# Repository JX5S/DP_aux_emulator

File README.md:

# DP-aux emulator

Hardware design files for a DP-aux emulation board, designed to allow connection of PSVR2 headsets to PC.

# Why

Prior to a March 2024 update of the PSVR2's firmware, the headset reported incorrect information via DP-aux, among others the EDID and DSC capability. A custom EDID can be set without additional hardware, however DSC options cannot be - so the emulator board was born.

# Status as of June 2024

Since this board was built, Sony released firmware update(s) to the PSVR2, which corrected the lies and allow connection to GPUs directly. While this emulator is still useful for enabling "cinema" mode and for future experiments, such as possibly enabling HDR support, most users won't need it.

This board is only for modifying traffic on DP-aux, it doesn't help if your GPU doesn't have a USB-C port. Sony is releasing an adapter for that soon, I have no reason to believe it wouldn't work with 3rd party drivers.

This is a third revision of the PCB, it has been verified to work as designed.

# Everything you need to build some

## PCBs

The board was designed for JLCPCB's assembly. The necessary files are in the ['Manufacturing data'](https://github.com/JX5S/DP_aux_emulator/tree/main/Manufacturing%20data) folder. The zip file is there for a quick download of just those 3 files. The files are:

- ...-Gerbers.zip = Manufacturing data for the circuit board
- ...-BOM.csv = a list of components that need mounting
- ...-top-pos.csv = a list of positions of each component

The only settings that need changing from defaults during ordering at JLCPCB are PCB thickness (0.8mm) and impedance control (Yes; JLC06081H-2116). Detailed screenshots of all settings including defaults are in the ['JLCPCB settings'](https://github.com/JX5S/DP_aux_emulator/tree/main/JLCPCB%20settings) folder.

The 4th image shows edge-rail cut-outs which need to be added to allow surface mounting of these specific USB-C connectors. These can be added by JLC (you do need to explicitly request them), or you can add them yourself in KiCad, or you can have the edge-rails removed and the USB-C connectors added afterwards (JLC will build a mounting adapter for the board at additional cost).

## Firmware

Firmware was written by the autor of the [iVRy SteamVR driver](https://store.steampowered.com/app/992490). A passthrough-only version of the firmware is provided in this repository for testing, a PSVR2-specific firmware is distributed along with the [iVRy PSVR2 driver](https://store.steampowered.com/app/2772740).

## 3D-Printed case

A case has been designed for the DP-AUX emulator by "Hackinside". They have kindly [made the files available](https://www.pcbway.com/project/shareproject/iVRy_PSVR2_DP_AUX_Emulator_Enclosure_case_ef058b5b.html) for anyone that wants to print their own case.

# How it works

On the PCB is an RP2040 microcontroller, which decides which DP-aux requests to modify and which to pass through unchanged. To interface with DP-aux, a pair of SN65MLVD200A differential transceivers are used. The LVDS part of the circuit is based on Bitec's DisplayPort Daughter Card.

Apart from the core DP-aux emulation circuitry, there is a programming micro-USB connector (I would have used a USB-C, but this way it cannot be confused with the PSVR2 port), orientation detection using USB-C CC pins, and a power section, allowing the board to be powered with either the programming USB port or using VBUS from the USB-Cs. Even though the board was made with specifically the PSVR2 in mind, I tried to make it as compliant as possible with a low part count and it should work well with the maximum voltage of USB-PD3.0, 21V.

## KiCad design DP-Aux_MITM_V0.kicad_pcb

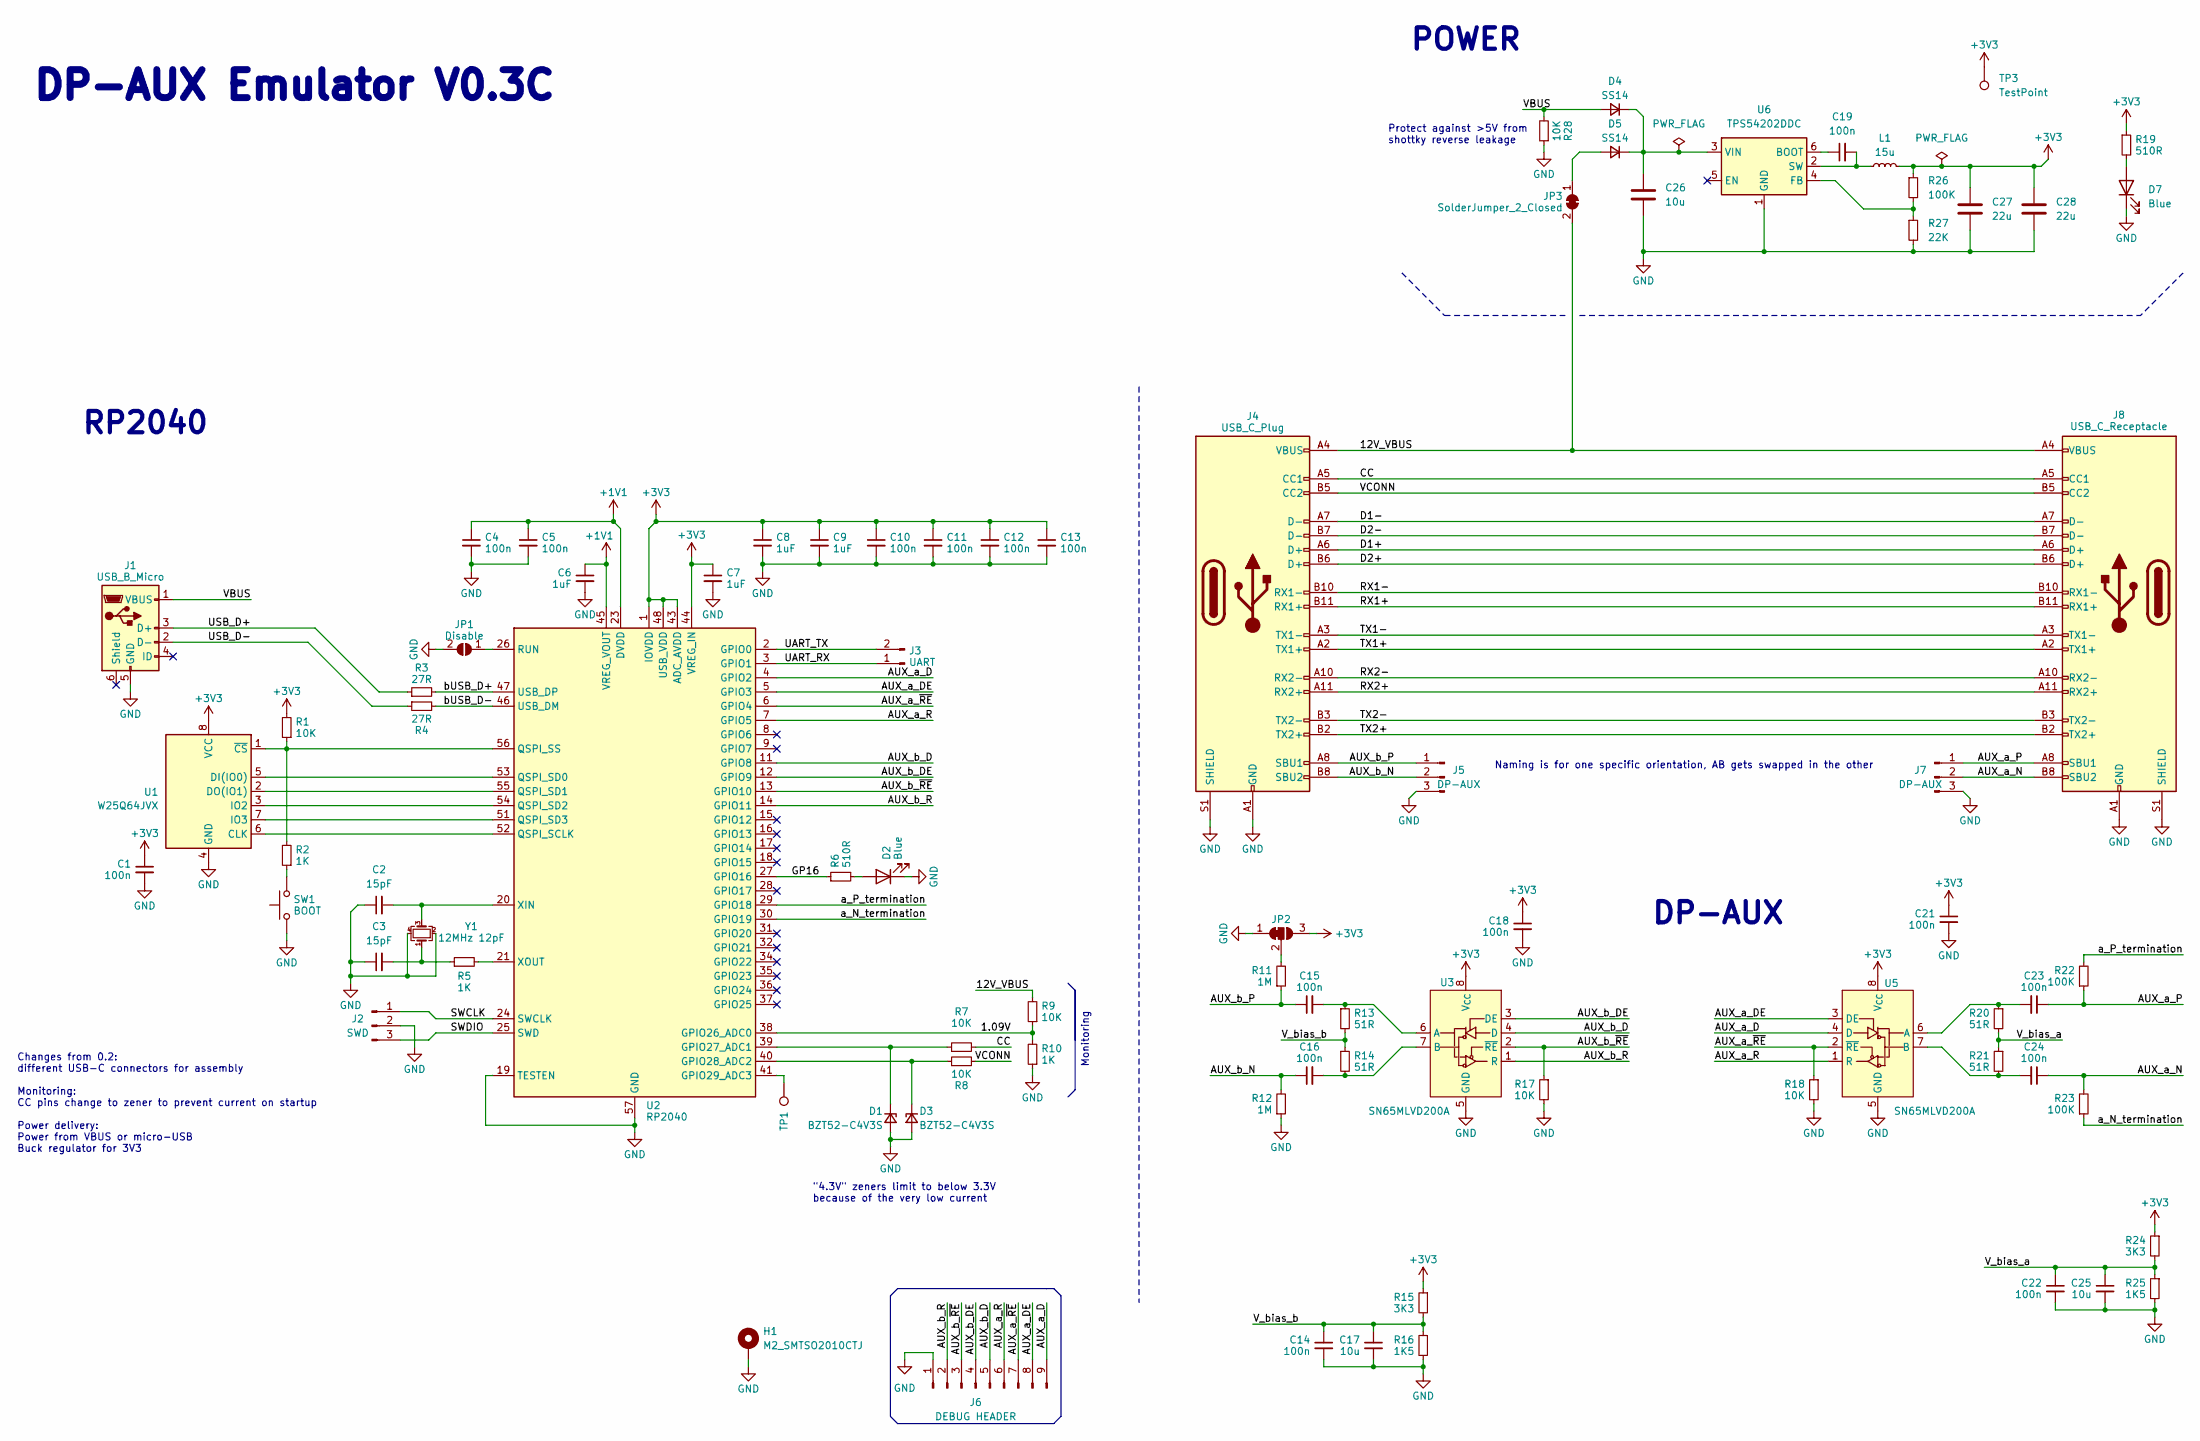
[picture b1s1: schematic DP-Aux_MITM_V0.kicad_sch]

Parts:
C1, C4, C5, C10, C11, C12, C13, C14, C15, C16, C18, C19, C21, C22, C23, C24: 100n; C_0402_1005Metric; LCSC C307331
C2, C3: 15pF; C_0402_1005Metric; LCSC C1548
C6, C7, C8, C9: 1uF; C_0402_1005Metric; LCSC C52923
C17, C25: 10u; C_0603_1608Metric; LCSC C19702
C26: 10u; C_0805_2012Metric; LCSC C15850
C27, C28: 22u; C_0805_2012Metric; LCSC C45783
D1, D3: BZT52-C4V3S; D_SOD-323 Panjit; LCSC C398771
D2, D7: Blue; LED_0603_1608Metric; LCSC C72041
D4, D5: SS14; D_SOD-123FL; LCSC C2909920
H1: M2_SMTSO2010CTJ; M2 solder nut; LCSC C2916319
J1: USB_B_Micro; USB_Micro-B_Molex-105017-0001; LCSC C132563
J2: SWD; PinHeader_1x03_P2.54mm_Vertical; LCSC DNP
J3: UART; PinHeader_1x02_P2.54mm_Vertical; LCSC DNP
J4: USB_C_Plug; USB_C_VirtualLink_Plug; LCSC C319150
J5, J7: DP-AUX; PinHeader_1x03_P2.54mm_Vertical; LCSC DNP
J6: DEBUG HEADER; PinHeader_1x09_P2.54mm_Vertical; LCSC DNP
J8: USB_C_Receptacle; USB_C_Straddle_Socket; LCSC C309352
JP1: Disable; SolderJumper-2_P1.3mm_Open_RoundedPad1.0x1.5mm; LCSC DNP
JP2: SolderJumper_3_Bridged12; SolderJumper-3_P1.3mm_Bridged2Bar12_RoundedPad1.0x1.5mm; LCSC DNP
JP3: SolderJumper_2_Closed; SolderJumper-2_P1.3mm_Bridged2Bar_RoundedPad1.0x1.5mm; LCSC DNP
L1: 15u; L_Sunlord_SWPA4018S; LCSC C436651
R1, R7, R8, R9, R17, R18, R28: 10K; R_0402_1005Metric; LCSC C25744
R2, R5, R10: 1K; R_0402_1005Metric; LCSC C11702
R3, R4: 27R; R_0603_1608Metric; LCSC C25190
R6, R19: 510R; R_0402_1005Metric; LCSC C25123
R11, R12: 1M; R_0402_1005Metric; LCSC C26083
R13, R14, R20, R21: 51R; R_0402_1005Metric; LCSC C25125
R15, R24: 3K3; R_0402_1005Metric; LCSC C25890
R16, R25: 1K5; R_0402_1005Metric; LCSC C25867
R22, R23, R26: 100K; R_0402_1005Metric; LCSC C25741
R27: 22K; R_0402_1005Metric; LCSC C25768
SW1: BOOT; C&K KMR223GLFG; LCSC C221678
TP1: TestPoint; TestPoint_Pad_D2.0mm; LCSC DNP
TP3: TestPoint; TestPoint_Loop_D1.80mm_Drill1.0mm_Beaded; LCSC C238122
U1: W25Q64JVX; WSON-8-1EP_4x4mm_P0.8mm_EP2.6x3mm; LCSC C2940195
U2: RP2040; QFN-56-1EP_7x7mm_P0.4mm_EP3.2x3.2mm; LCSC C2040
U3, U5: SN65MLVD200A; SOIC-8_3.9x4.9mm_P1.27mm; LCSC SN65MLVD200A
U6: TPS54202DDC; SOT-23-6; LCSC C191884
Y1: 12MHz 12pF; Crystal_SMD_2520-4Pin_2.5x2.0mm; LCSC C479184

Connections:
+1V1: C4.1, C5.1, C6.1, U2.23 (DVDD), U2.45 (VREG_VOUT), U2.50 (DVDD)
+3V3: C1.1, C7.1, C8.1, C9.1, C10.1, C11.1, C12.1, C13.1, C18.1, C21.1, C27.1, C28.1, JP2.3 (B), L1.2, R1.2, R15.1, R19.1, R24.1, R26.1, TP3.1, U1.8 (VCC), U2.1 (IOVDD), U2.10 (IOVDD), U2.22 (IOVDD), U2.33 (IOVDD), U2.42 (IOVDD), U2.43 (ADC_AVDD), U2.44 (VREG_IN), U2.48 (USB_VDD), U2.49 (IOVDD), U3.8 (V_{CC}), U5.8 (V_{CC})
/1.09V: R9.1, R10.2, U2.38 (GPIO26_ADC0)
/12V_VBUS: J4.A4 (VBUS), J4.A9 (VBUS), J4.B4 (VBUS), J4.B9 (VBUS), J8.A4 (VBUS), J8.A9 (VBUS), J8.B4 (VBUS), J8.B9 (VBUS), JP3.2 (B), R9.2
/AUX_a_D: J6.9, U2.4 (GPIO2), U5.4 (D)
/AUX_a_DE: J6.8, U2.5 (GPIO3), U5.3 (DE)
/AUX_a_N: C24.1, J7.2, J8.B8 (SBU2), R23.2
/AUX_a_P: C23.1, J7.1, J8.A8 (SBU1), R22.1
/AUX_a_R: J6.6, U2.7 (GPIO5), U5.1 (R)
/AUX_a_~RE: J6.7, R18.1, U2.6 (GPIO4), U5.2 (~RE)
/AUX_b_D: J6.5, U2.11 (GPIO8), U3.4 (D)
/AUX_b_DE: J6.4, U2.12 (GPIO9), U3.3 (DE)
/AUX_b_N: C16.1, J4.B8 (SBU2), J5.2, R12.2
/AUX_b_P: C15.1, J4.A8 (SBU1), J5.1, R11.1
/AUX_b_R: J6.2, U2.14 (GPIO11), U3.1 (R)
/AUX_b_~RE: J6.3, R17.1, U2.13 (GPIO10), U3.2 (~RE)
/CC: J4.A5 (CC1), J8.A5 (CC1), R7.2
/D1+: J4.A6 (D+), J8.A6 (D+)
/D1-: J4.A7 (D-), J8.A7 (D-)
/D2+: J4.B6 (D+), J8.B6 (D+)
/D2-: J4.B7 (D-), J8.B7 (D-)
/GP16: R6.1, U2.27 (GPIO16)
/RX1+: J4.B11 (RX1+), J8.B11 (RX1+)
/RX1-: J4.B10 (RX1-), J8.B10 (RX1-)
/RX2+: J4.A11 (RX2+), J8.A11 (RX2+)
/RX2-: J4.A10 (RX2-), J8.A10 (RX2-)
/SWCLK: J2.1, U2.24 (SWCLK)
/SWDIO: J2.3, U2.25 (SWD)
/TX1+: J4.A2 (TX1+), J8.A2 (TX1+)
/TX1-: J4.A3 (TX1-), J8.A3 (TX1-)
/TX2+: J4.B2 (TX2+), J8.B2 (TX2+)
/TX2-: J4.B3 (TX2-), J8.B3 (TX2-)
/UART_RX: J3.1, U2.3 (GPIO1)
/UART_TX: J3.2, U2.2 (GPIO0)
/USB_D+: J1.3 (D+), R3.1
/USB_D-: J1.2 (D-), R4.1
/VBUS: D4.2 (A), J1.1 (VBUS), R28.2
/VCONN: J4.B5 (CC2), J8.B5 (CC2), R8.2
/V_bias_a: C22.1, C25.1, R20.2, R21.1, R24.2, R25.1
/V_bias_b: C14.1, C17.1, R13.2, R14.1, R15.2, R16.1
/a_N_termination: R23.1, U2.30 (GPIO19)
/a_P_termination: R22.2, U2.29 (GPIO18)
/bUSB_D+: R3.2, U2.47 (USB_DP)
/bUSB_D-: R4.2, U2.46 (USB_DM)
GND: C1.2, C2.1, C3.1, C4.2, C5.2, C6.2, C7.2, C8.2, C9.2, C10.2, C11.2, C12.2, C13.2, C14.2, C17.2, C18.2, C21.2, C22.2, C25.2, C26.2, C27.2, C28.2, D1.2 (A), D2.1 (K), D3.2 (A), D7.1 (K), H1.1, J1.5 (GND), J2.2, J4.A1 (GND), J4.A12 (GND), J4.B1 (GND), J4.B12 (GND), J4.S1 (SHIELD), J5.3, J6.1, J7.3, J8.A1 (GND), J8.A12 (GND), J8.B1 (GND), J8.B12 (GND), J8.S1 (SHIELD), JP1.2 (B), JP2.1 (A), R10.1, R12.1, R16.2, R17.2, R18.2, R25.2, R27.2, R28.1, SW1.1, U1.4 (GND), U2.19 (TESTEN), U2.57 (GND), U3.5 (GND), U5.5 (GND), U6.1 (GND), Y1.2, Y1.4
unnamed: C3.2, R5.1, Y1.1
unnamed: D1.1 (K), R7.1, U2.39 (GPIO27_ADC1)
unnamed: D2.2 (A), R6.2
unnamed: D3.1 (K), R8.1, U2.40 (GPIO28_ADC2)
unnamed: C26.1, D4.1 (K), D5.1 (K), U6.3 (VIN)
unnamed: D5.2 (A), JP3.1 (A)
unnamed: D7.2 (A), R19.2
unnamed: JP1.1 (A), U2.26 (RUN)
unnamed: JP2.2 (C), R11.2
unnamed: R2.1, SW1.2
unnamed: U1.6 (CLK), U2.52 (QSPI_SCLK)
unnamed: U1.5 (DI(IO0)), U2.53 (QSPI_SD0)
unnamed: U1.2 (DO(IO1)), U2.55 (QSPI_SD1)
unnamed: U1.3 (IO2), U2.54 (QSPI_SD2)
unnamed: U1.7 (IO3), U2.51 (QSPI_SD3)
unnamed: R1.1, R2.2, U1.1 (~CS), U2.56 (QSPI_SS)
unnamed: TP1.1, U2.41 (GPIO29_ADC3)
unnamed: C2.2, U2.20 (XIN), Y1.3
unnamed: R5.2, U2.21 (XOUT)
unnamed: C15.2, R13.1, U3.6 (A)
unnamed: C16.2, R14.2, U3.7 (B)
unnamed: C23.2, R20.1, U5.6 (A)
unnamed: C24.2, R21.2, U5.7 (B)
unnamed: C19.1, U6.6 (BOOT)
unnamed: R26.2, R27.1, U6.4 (FB)
unnamed: C19.2, L1.1, U6.2 (SW)

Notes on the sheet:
RP2040
DP-AUX
Naming is for one specific orientation, AB gets swapped in the other
Changes from 0.2: different USB-C connectors for assembly Monitoring: CC pins change to zener to prevent current on startup Power delivery: Power from VBUS or micro-USB Buck regulator for 3V3
Protect against >5V from shottky reverse leakage
POWER
DP-AUX Emulator V0.3C
Monitoring
"4.3V" zeners limit to below 3.3V because of the very low current

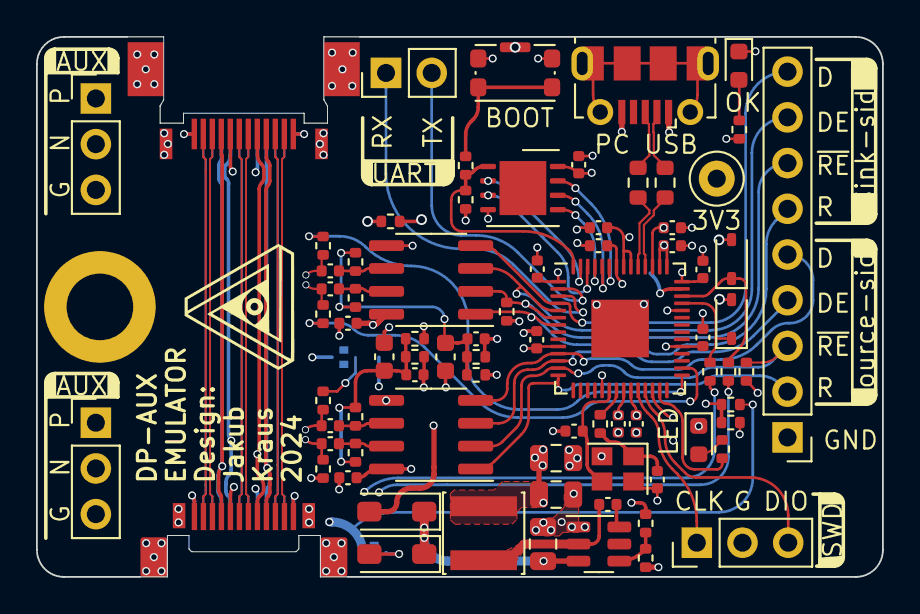
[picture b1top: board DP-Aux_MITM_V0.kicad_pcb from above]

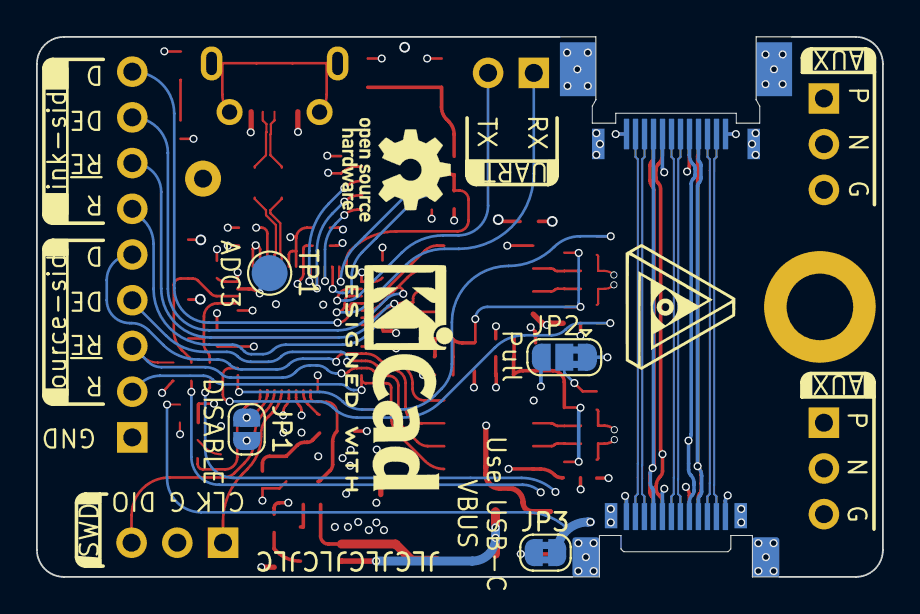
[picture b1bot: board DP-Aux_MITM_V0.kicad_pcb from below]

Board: 6 copper layers, 47.0 x 30.0 mm, 83 parts (4 on the bottom side), 71 nets.

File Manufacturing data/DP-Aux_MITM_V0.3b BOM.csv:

"Item","Qty","Reference(s)","Value","LibPart","Footprint","Datasheet","DNP","LCSC","Sim.Device","Sim.Pins"
"1","16","C1, C4, C5, C10, C11, C12, C13, C14, C15, C16, C18, C19, C21, C22, C23, C24","100n","Device:C_Small","Capacitor_SMD:C_0402_1005Metric","~","","C307331","",""
"2","2","C2, C3","15pF","Device:C_Small","Capacitor_SMD:C_0402_1005Metric","~","","C1548","",""
"3","4","C6, C7, C8, C9","1uF","Device:C_Small","Capacitor_SMD:C_0402_1005Metric","~","","C52923","",""
"4","2","C17, C25","10u","Device:C_Small","Capacitor_SMD:C_0603_1608Metric","~","","C19702","",""
"5","1","C26","10u","Device:C","Capacitor_SMD:C_0805_2012Metric","~","","C15850","",""
"6","2","C27, C28","22u","Device:C","Capacitor_SMD:C_0805_2012Metric","~","","C45783","",""
"7","2","D1, D3","BZT52-C4V3S","Device:D_Zener_Small","USB-C_for_0.3:D_SOD-323 Panjit","~","","C398771","",""
"8","2","D2, D7","Blue","Device:LED","LED_SMD:LED_0603_1608Metric","~","","C72041","",""
"9","2","D4, D5","SS14","Device:D_Small","USB-C_for_0.2:D_SOD-123FL","~","","C2909920","D","1=K 2=A"
"11","1","H1","M2_SMTSO2010CTJ","Mechanical:MountingHole_Pad","M2nutV2:M2 solder nut","https://datasheet.lcsc.com/lcsc/2112061830_Sinhoo-SMTSO2010C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","","C2916319","",""
"12","1","J1","USB_B_Micro","Connector:USB_B_Micro","Connector_USB:USB_Micro-B_Molex-105017-0001","~","","C132563","",""
"15","1","J4","USB_C_Plug","Connector:USB_C_Receptacle","USB-C_for_0.3:USB_C_VirtualLink_Plug","https://datasheet.lcsc.com/lcsc/2002271811_XKB-Connectivity-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",""," C319150","",""
"18","1","J8","USB_C_Receptacle","Connector:USB_C_Receptacle","USB-C_for_0.3:USB_C_Straddle_Socket","https://www.lcsc.com/product-detail/USB-Connectors_HOOYA-USB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","","C309352","",""
"22","1","L1","15u","Device:L_Small","Inductor_SMD:L_Sunlord_SWPA4018S","~","","C436651","",""
"23","7","R1, R7, R8, R9, R17, R18, R28","10K","Device:R_Small","Resistor_SMD:R_0402_1005Metric","~","","C25744","",""
"24","3","R2, R5, R10","1K","Device:R_Small","Resistor_SMD:R_0402_1005Metric","~","","C11702","",""
"25","2","R3, R4","27R","Device:R_Small","Resistor_SMD:R_0603_1608Metric","~","","C25190","",""
"26","2","R6, R19","510R","Device:R_Small","Resistor_SMD:R_0402_1005Metric","~","","C25123","",""
"27","2","R11, R12","1M","Device:R_Small","Resistor_SMD:R_0402_1005Metric","~","","C26083","",""
"28","4","R13, R14, R20, R21","51R","Device:R_Small","Resistor_SMD:R_0402_1005Metric","~","","C25125","",""
"29","2","R15, R24","3K3","Device:R_Small","Resistor_SMD:R_0402_1005Metric","~","","C25890","",""
"30","2","R16, R25","1K5","Device:R_Small","Resistor_SMD:R_0402_1005Metric","~","","C25867","",""
"31","3","R22, R23, R26","100K","Device:R_Small","Resistor_SMD:R_0402_1005Metric","~","","C25741","",""
"32","1","R27","22K","Device:R_Small","Resistor_SMD:R_0402_1005Metric","~","","C25768","",""
"33","1","SW1","BOOT","Switch:SW_Push","USB-C_for_0.3:C&K KMR223GLFG","~","","C221678","",""
"36","1","U1","W25Q64JVX","Memory_Flash:W25Q128JVS","Package_SON:WSON-8-1EP_4x4mm_P0.8mm_EP2.6x3mm","http://www.winbond.com/resource-files/w25q128jv_dtr%20revc%2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","","C2940195","",""
"37","1","U2","RP2040","MCU_RaspberryPi:RP2040","Package_DFN_QFN:QFN-56-1EP_7x7mm_P0.4mm_EP3.2x3.2mm","https://datasheets.raspberrypi.com/rp2040/rp2040-datasheet.pdf","","C2040","",""
"38","2","U3, U5","SN65MLVD200A","diff_transceiver:SN65MLVD200A","Package_SO:SOIC-8_3.9x4.9mm_P1.27mm","https://www.ti.com/lit/ds/symlink/sn65mlvd200a.pdf?ts=1700755286435","","SN65MLVD200A","",""
"39","1","U6","TPS54202DDC","Regulator_Switching:TPS54202DDC","Package_TO_SOT_SMD:SOT-23-6","http://www.ti.com/lit/ds/symlink/tps54202.pdf","","C191884","",""
"40","1","Y1","12MHz 12pF","Device:Crystal_GND24_Small","Crystal:Crystal_SMD_2520-4Pin_2.5x2.0mm","https://datasheet.lcsc.com/lcsc/2304140030_YXC-X322512MSB4SI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","","C479184","",""

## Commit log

2024-03-05 Create LICENSE
2024-03-25 Added Readme, render
2024-03-25 Update README.md
    Added status
2024-06-21 Add JLCPCB reference options
